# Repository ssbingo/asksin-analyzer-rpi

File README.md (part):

# AskSin-Analyzer

Ein dauerhaft laufender **Funkanalyzer für Homematic (BidCoS, 868 MHz)** auf
Raspberry-Pi-Basis: eine eigene Empfängerplatine hört den Funkverkehr passiv
mit, ein Node.js-Dienst auf dem Pi wertet aus (Duty-Cycle, RSSI,
Telegrammraten), eine Web-UI zeigt an, und ein ioBroker-Adapter spiegelt die
Ergebnisse in die Hausautomation. Mehrere Geräte an verschiedenen Standorten
im Haus sind ausdrücklich vorgesehen.

📖 **[Handbuch (PDF)](docs/handbuch/AskSin-Analyzer-Handbuch.pdf)** — die
anfängertaugliche Schritt-für-Schritt-Anleitung vom Platinenbestellen bis zum
laufenden Gerät.

> ### ⚠️ Platinen mit „HW v0.0.1" im Bestückungsdruck
>
> Bei diesen ist die 2×20-Buchse J1 gespiegelt — direkt aufgesteckt liegt
> jedes Pad auf dem falschen Pi-Pin (5 V auf 3,3 V, Masse auf GPIOs).
> **Nicht ohne den [J1-Rettungsadapter](hardware/kicad/adapter/README.md)
> aufstecken und einschalten.** Mit ihm sind sie voll funktionsfähig.
> Ab **v0.2.0** ist der Fehler behoben, und die Platine liegt neben dem Pi
> statt über dessen Buchsen.

## Projektstand

| Baustein | Stand |
| --- | --- |
| **Hardware v0.2.0** (L-Platine neben dem Pi) | ✅ **in Produktion** (31.07.2026) — DRC/ERC 0/0, 26 Fertigungsprüfungen bestanden |
| Fertigungsdaten (Gerber, BOM, CPL, JLCPCB) | ✅ [`hardware/kicad/fab/`](hardware/kicad/fab/) + Archiv |
| J1-Rettungsadapter für die Chargen v0.0.1 | ✅ [`hardware/kicad/adapter/`](hardware/kicad/adapter/README.md) |
| Firmware | ✅ abgewandelte Fassung des `AskSinSniffer328P` (jp112sdl) — läuft auch ohne Funkmodul und meldet dessen Fehlen, [eigenes Repo](https://github.com/ssbingo/asksin-sniffer-firmware); Prüfwerkzeuge in [`firmware/`](firmware/README.md) |
| Firmware, erweiterte Fassung | 🔨 gebaut, wartet auf die Platine — eigenes Repo [`asksin-sniffer-firmware`](https://github.com/ssbingo/asksin-sniffer-firmware): Versionsauskunft, Folgenummer, Prüfsumme, CC1101-Selbsttest. Im Auslieferungszustand Zeichen für Zeichen wie das Original |
| Mitschnitt der Funkstrecke | ✅ Grundlinie vor Firmware-Änderungen, Schalter unter *Wartung* (F1) |
| Core: Parser + Duty-Cycle | ✅ fertig ([`core/`](core/)) |
| Core: Serial-Ingest, SQLite, CCU-Namen, Analyzer | ✅ fertig verdrahtet (M2–M4) |
| Core: REST-API inkl. XS-Kompat-Endpunkten | ✅ fertig, 108 Unit-Tests gesamt (M5) |
| Web-UI (Nachbau, eigener Code, MIT) | ✅ fertig: Vue 3 + ECharts, vom Core ausgeliefert (M5.5) |
| Demo-Modus (simulierte Anlage) | ✅ fertig, Schalter in den Einstellungen (v0.0.3) |
| Update-Pfade (Core-Self-Update, 328P-Flash) | ✅ fertig (M7.5, v0.0.4) |
| Netzwerkeinstellungen über die Web-UI | ✅ gebaut (M7.6) — Praxistest auf dem Pi ausstehend |
| Status-LED + OLED integriert | ✅ Software fertig (M11) — Hardware-Test steht aus ([`docs/status-led-oled.md`](docs/status-led-oled.md)) |
| Einkaufsführer Zubehör (README + Handbuch) | 📋 geplant (M12, [`docs/einkaufsfuehrer.md`](docs/einkaufsfuehrer.md)) |
| Verbund: 5 Analyzer als Gesamtsystem | ✅ komplett: Dashboard, Matrix+Dedup, Flotten-Update, Langzeitdaten nach InfluxDB (M9.1–M9.5, [`docs/verbund.md`](docs/verbund.md)) |
| Langzeitdaten vor Ort (InfluxDB + Grafana) | ✅ optional auf dem Master: Ein-Klick-Einrichtung, acht fertige Grafana-Ansichten, vier Alarme (M14) |
| Bootmedium | SSD ab Pi 4; **der Pi 3 läuft von SD-Karte** (Netzwerk am USB-Bus, nur USB 2.0) |
| CCU-Verbindungstest mit Diagnose | ✅ nennt die Geräteanzahl, unterscheidet sechs Fehlerursachen und blendet bei fehlender Systemvariable die Einrichtung ein ([`ccu/`](ccu/README.md)) |
| Alarmziele: ioBroker, E-Mail, Telegram | ✅ in der WebUI einstellbar, mit Testversand und deutlichen Fehlermeldungen (M14.2) |
| Versionsabhängigkeit Analyzer ↔ Adapter | ✅ beide Seiten weisen sie aus **und prüfen sie** (M15) |
| Protokoll und Absturzsuche (Tab „Wartung“) | ✅ fertig (M13): Stufen, Tagesrotation, Download, Systemjournal ([`docs/protokoll.md`](docs/protokoll.md)) |
| ioBroker-Adapter | 🔨 Grundgerüst steht (M6, eigenes Repo [`ioBroker.asksinanalyzer-rpi`](https://github.com/ssbingo/ioBroker.asksinanalyzer-rpi), MIT, mehrinstanzfähig) |

## Installation auf dem Raspberry Pi

Ein Aufruf installiert und konfiguriert alles (Details: [`deploy/README.md`](deploy/README.md)):

```bash
curl -fsSL https://raw.githubusercontent.com/ssbingo/asksin-analyzer-rpi/main/install.sh | sudo bash
```

## Aufbau des Repositories

```
hardware/                 Platine, Bestelllisten, Setup-Skripte
├── README.md             vollständige Hardware-Spezifikation
├── bestellliste-reichelt.md
├── setup-uart.sh         richtet den Pi-UART ein (Pi 3/4/5)
├── 99-asksin-analyzer.rules   udev: fester Gerätename
├── 3d-druck/             Druckvorlagen 19″-Einbaurahmen (folgen nach Testdruck)
├── datasheets/           Ebyte-E07-Serienspezifikation
└── kicad/                KiCad-9-Projekt, generiert & maschinell geprüft
    ├── generate_*.py     Schaltplan, Layout, Symbole, Footprints, BOM/CPL
    ├── autoroute.py      Freerouting-Anbindung
    ├── rebuild.py       baut die Platine neu, bis alle Prüfungen sauber sind
    ├── adapter/         J1-Rettungsadapter für die Chargen v0.0.1
    ├── fab/             Gerber, Bohrdaten, BOM, CPL, PDFs
    └── AskSin-Analyzer-V3-fertigung.zip   Upload-Paket
core/                     Node.js/TypeScript-Analysedienst
webui/                    Web-UI-Nachbau (Vue 3 + ECharts, MIT)
deploy/                   systemd-Unit, Beispielkonfig, CLI-Wrapper
install.sh / update.sh    Ein-Befehl-Installation und -Update auf dem Pi
docs/
├── serial-protocol.md    das serielle Telegrammformat, verifiziert
├── raspberry-pi-uart.md  UART-Konfiguration Pi 3/4/5
├── webui-und-updates.md  API-Vertrag der Web-UI, Update-Pfade, Lizenzlage
├── verbund.md            Phase M9: fünf Analyzer als Gesamtsystem (Föderation)
├── protokoll.md          Phase M13: Protokoll, Systemjournal, Absturzsuche
├── status-led-oled.md    Phase M11: Status-LED (PWM/SPI) und OLED
└── handbuch/             das Handbuch (HTML-Quelle, Bilder, PDF)
reference/                Originalprojekte (nicht eingecheckt — siehe unten)
```

## Die Kernentscheidungen in einem Absatz

Die Funkseite bleibt beim bewährten Gespann **ATmega328P + CC1101** mit der
unveränderten `AskSinSniffer328P`-Firmware — kein Fork, wer will flasht die
Original-HEX. Die Platine ist ein **L-förmiger** Aufsatz, der auf den
durchgeschleiften Header des PoE-HAT gesteckt wird; der Streifen liegt
**parallel neben dem Pi** an der Header-Seite, höchstens 20 mm breit, und
deckt keine Buchse ab. Der Schenkel steht 32 mm **hinter** der SD-Kante —
dort sitzt das Funkmodul, weit weg vom Störnebel und direkt am rückwärtigen
Antennen-Keystone. Die Antenne verlässt das
Ebyte-Modul per IPEX — auf der Platine existiert **keine einzige HF-Leitung**.
Der bekannte 2,12-%-Baudratenfehler der 8-MHz-Klasse wird nicht in der
Firmware „repariert", sondern auf der Pi-Seite kompensiert: der Port läuft mit
**58824 Baud** (Details: [`hardware/README.md`](hardware/README.md),
Abschnitt 2.5 — das ist Absicht, nicht Tippfehler). Analyse-Software und
ioBroker-Adapter sind getrennt geschnitten, damit der Adapter frei lizenzierbar
und veröffentlichbar bleibt ([`docs/webui-und-updates.md`](docs/webui-und-updates.md),
Abschnitt 4).

## Schnellzugriffe

- **Platine nachbestellen:** `hardware/kicad/AskSin-Analyzer-V3-fertigung.zip`
  hochladen (4 Lagen, 1,6 mm); SMD-Bestückung mit
  `fab/jlcpcb_bom.csv` + `fab/jlcpcb_cpl.csv`
- **Bauteile kaufen:** [`hardware/bestellliste-reichelt.md`](hardware/bestellliste-reichelt.md)
- **Pi einrichten:** `sudo hardware/setup-uart.sh` → Neustart →
  `stty -F /dev/ttyAMA0 57600 raw -echo` — dann die exakte Rate:
  `sudo python3 deploy/baudrate.py /dev/ttyAMA0 58824 && cat -v /dev/ttyAMA0`
  (`stty` kennt nur genormte Raten und lehnt 58824 ab)
- **Core-Tests:** `cd core && npm install && npm run check`

## Versionierung

Ein Repository, drei unabhängige Zählungen über Tag-Präfixe:

| Tag | versioniert | aktuell |
| --- | --- | --- |
| `hardware-vX.Y.Z` | die Platine (Schaltplan, Layout, Fertigungsdaten) | **0.2.0** — steht auch im Bestückungsdruck |
| `core-vX.Y.Z` | die Pi-Software (`core/` + `webui/`, deren `package.json` führen dieselbe Nummer) | **1.2.0** |
| `vX.Y.Z` | den Gesamtstand des Projekts (Doku, Handbuch, Zusammenspiel) | **1.2.0** |

Die **Firmware hat ein eigenes Repository** mit eigener Versionierung:
[ssbingo/asksin-sniffer-firmware](https://github.com/ssbingo/asksin-sniffer-firmware).
Sie war ursprünglich die unveränderte `AskSinSniffer328P` von jp112sdl; seit
den Erweiterungen um Folgenummer, Prüfsumme, Versionsauskunft und
Funkmodul-Selbsttest ist sie eine abgewandelte Fassung und wird als solche
gepflegt — Lizenz unverändert CC BY-NC-SA 3.0. Der ioBroker-Adapter bekommt
ebenfalls ein eigenes Repository mit eigenständiger Versionierung.

## Changelog

### v1.8.0 — 26.08.2026

**Neue Ansicht „Funklast": Wer verbraucht die Sendezeit — und wie viel davon war umsonst?**

Entstanden aus einem echten Fall: Die CCU meldete für ein LAN-Gateway einen
Duty-Cycle über 100 %, und die Ursache zu finden kostete eine Stunde Handarbeit
an der Datenbank. Dieselbe Kette läuft jetzt automatisch — an denselben Daten
gemessen in **53 ms**.

- Die Spalten stehen in der Reihenfolge der Ursachen: **Sendezeit → Bursts →
  Wiederholungen → vergebliche Wiederholungen.** Ein Absender fällt durch
  Sendezeit auf, nicht durch die Zahl der Telegramme; im Fall stieg die Zahl von
  219 auf 345, die Sendezeit aber von 4,6 s auf 30 s.
- **„Vergeblich" kann nur ein Mithörer füllen:** Wiederholungen, obwohl der
  Analyzer die Antwort bereits gehört hatte. Eine Zentrale sieht nur, dass sie
  wiederholen muss — nicht, ob die Antwort unterwegs verloren ging. Steht dort
  eine hohe Zahl, ist der Rückweg das Nadelöhr, und man sucht am Absender statt
  am Gerät.
- **Mehrere Sender unter einer Adresse werden getrennt.** Alle LAN-Gateways
  einer CCU senden mit deren Adresse; auseinanderhalten lässt sie nur die
  Empfangsstärke. Im Fall: zwei Gipfel, 30 dB auseinander, und 78 von 81 Bursts
  aus dem lauten — damit war das schuldige Gateway benannt, unabhängig von der
  CCU-Anzeige.
- Aufklappen zeigt je Gegenstelle die Sendungen je Vorgang, die Bursts, die
  vergeblichen Wiederholungen und wie laut der Analyzer die **Antworten** hört.
  Dazu ein Satz, was zu tun ist — nicht nur, was gemessen wurde.
- Zehn Tests, darunter der komplette Fall als Durchlauf. Zwei Fehler fanden sie
  beim Schreiben: HmIP beginnt bei Typ 0x80 (mein Testwert 0x5E war das
  Leistungstelegramm eines Schaltaktors und prüfte nichts), und ein Gerät, das
  in einem Fenster **nur quittiert**, fiel ganz aus der Liste — seine Sendezeit
  belegt das Band trotzdem.
- Handbuch 13.4 liest den Fall Zeile für Zeile mit; 13.5 und 13.6 rücken auf.

### v1.7.3 — 25.08.2026

**Nachtrag zur „Sammlung": Der Master fragte sich selbst über HTTP.**

In v1.7.2 lief der Master beim Zählen über *alle* Peers — und die Liste enthält
ihn selbst. Sein Aufruf von `/api/langzeitdaten` rief also wieder die Zählung
auf, die wieder sich selbst aufrief. Das endet erst in Zeitüberschreitungen, und
die Kachel zeigte danach wieder einen Strich — aus dem genau umgekehrten Grund
als vorher.

- Der eigene Standort wird jetzt **direkt** genommen, ohne HTTP; nur die
  entfernten Peers werden gefragt.
- Ein Test hält es fest, gegengeprüft.
- Nebenbei die Wortwahl berichtigt: Ein Analyzer ohne Schreibvorgang heißt
  „liefert gerade nicht" statt „seit Längerem still". Direkt nach jeder
  Aktualisierung steht dort für einen Schreibtakt lang auch ein völlig gesundes
  Gerät — beobachtet an Dachboden unmittelbar nach dem Rollout.

### v1.7.2 — 25.08.2026

**„Sammlung" zeigt wieder, wie viele Standorte liefern — statt eines Strichs.**

Gemeldet: „Was sollte eigentlich bei dem Punkt *Sammlung* stehen? Dort ist
bisher nur ein Strich zu finden." Antwort: **3 Standorte**. Dass dort nichts
stand, war ein stiller Fehler aus unserer eigenen Token-Trennung.

Die Zeile zählte die Standorte mit einer Flux-Abfrage. Die lief — bis Grafana
einen **Lese**- und die Analyzer einen **Schreib**-Token bekamen. Seither sieht
ein Analyzer den Bucket nicht mehr, und InfluxDB antwortet nicht mit „verboten",
sondern mit `HTTP 404 could not find bucket`. Der `catch` machte daraus ein
stilles „nicht ermittelbar".

- **Gezählt werden jetzt die Analyzer, nicht die Datenbank.** Jeder weiß über
  sich selbst, ob und wann sein letzter Schreibvorgang geglückt ist; der Master
  fragt der Reihe nach alle ab. Kein Lesezugriff nötig — die Token-Trennung
  bleibt, wie sie ist.
- Der ursprüngliche Anspruch bleibt: **Ein Standort zählt nur, wenn er wirklich
  schreibt.** Fehlt einer, steht dort *2 von 3 Standorten*; wer fehlt, zeigt der
  Mauszeiger.
- Ein Standort gilt erst nach **drei Schreibtakten** ohne Erfolg als still,
  mindestens aber nach fünf Minuten — ein einzelner Aussetzer darf die Anzeige
  nicht flackern lassen.
- `tools/pruefe-influx-lesezugriff.sh` hält fest, dass der Core nicht wieder
  anfängt zu lesen. Gegengeprüft.
- Handbuch 19.6 erklärt die ganze Kachel und warum nicht die Datenbank gefragt
  wird.

### v1.7.1 — 24.08.2026

**Die Clients melden jetzt über den Master.**

Damit fällt die Grenze aus v1.7.0: Bisher meldete sich nur der Master, weil nur
dort ein Alarmziel eingerichtet wird.

- **Der Master holt ab, die Clients senden nicht.** Das folgt der Richtung, die
  der Verbund ohnehin hat: Der Master kennt jeden Client samt Token, die Clients
  kennen den Master nicht. Ein Push bräuchte auf jedem Client Adresse und
  Geheimnis des Masters — neue Einstellungen, die jemand pflegen muss. So kommt
  die Weiterleitung **ohne eine einzige neue Einstellung** aus.
- **In der Nachricht steht der Standort des Clients**, nicht der des Masters.
  Der Master reicht den Text weiter, den der Client selbst gebaut hat.
- **Nichts geht verloren:** Der Client hakt eine Meldung erst ab, wenn der
  Master die Zustellung bestätigt hat. Ist der Master aus, bleibt sie liegen und
  geht beim nächsten Umlauf hinaus. Angestaut wird nichts — es gibt immer nur
  den letzten Lauf.
- **Die Nachricht nennt jetzt das Datum des Laufs**, nicht nur die Dauer: Eine
  verspätete Weiterleitung läse sich sonst so, als sei es eben erst passiert.
- Zwei Tests halten den Vertrag fest: dass beide Seiten die Abhak-Schnittstelle
  gleich verstehen (`httpPost` schickt bewusst keinen Rumpf, die Aktion steht
  in der Abfragezeichenkette), und dass der Master **erst zustellt und dann
  abhakt**. Beides gegengeprüft.

### v1.7.0 — 24.08.2026

**Der Analyzer meldet, wenn eine Systemaktualisierung durchgelaufen ist.**

Auf Wunsch — dritter Schalter im selben Feld. Zugestellt über **dasselbe Ziel,
das schon für die Alarme eingerichtet ist**: ioBroker-Adapter, E-Mail oder
Telegram. Ist dort nichts eingerichtet oder der Versand aus, bleibt der Schalter
ausgegraut, mit dem Hinweis wo man das ändert; ein Schalter, der sich umlegen
lässt und nichts bewirkt, wäre schlimmer als keiner.

- **Der Adapter braucht keine Änderung.** Die Meldung geht im
  Grafana-Webhook-Format hinaus, also in genau der Form, die er für die Alarme
  ohnehin versteht.
- **Erfolg und Fehlschlag** werden gemeldet. Der Fehlschlag ist der wichtigere
  Fall: Ein Gerät, das seit Wochen vergeblich aktualisiert, sieht von außen aus
  wie eines, das brav aktualisiert.
- Die Nachricht nennt Standort, Paketanzahl, Dauer und ob ein Neustart nötig
  ist. War nichts nachzuholen, steht das ausdrücklich da — „0 Pakete" allein
  liesse den Empfänger raten, ob die Meldung abgeschnitten ist.
- **Eine Entwarnung folgt sofort nach.** Sonst bliebe `alarm.aktiv` im Adapter
  dauerhaft auf *wahr*, denn eine abgeschlossene Aktualisierung ist ein Ereignis
  und kein andauernder Zustand. Weitergeleitet wird die Entwarnung nur, wenn man
  das ausdrücklich eingestellt hat — es kommt also genau eine Nachricht an.
- **Übersteht den Neustart des Dienstes mitten im Lauf:** apt rüstet auch
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
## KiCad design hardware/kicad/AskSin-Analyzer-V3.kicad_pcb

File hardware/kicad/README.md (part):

# KiCad-Projekt AskSin-Analyzer V4

KiCad 9. Schaltplan und Layout werden **generiert**, geroutet wird mit
Freerouting.

Stand: **ERC 0 Fehler, 0 Warnungen · DRC 0 Verstöße.** Netzliste stimmt exakt
mit der Spezifikation überein — 32 Bauteile, 25 Netze, 111 Anschlüsse. Platine
vollständig verdrahtet: 330 Leiterbahnen, 157 Durchkontaktierungen, vier Lagen.

## Ablauf

```bash
python3 generate_module_symbol.py     # Symbol des Funkmoduls
python3 generate_module_footprint.py  # Footprint des Funkmoduls
python3 generate_schematic.py         # Schaltplan, Projektdateien, netlist.md
python3 generate_pcb.py               # Umriss, Platzierung, Netze, Flächen
python3 autoroute.py                  # Freerouting + Flächenanbindung

kicad-cli sch erc --output erc.rpt --severity-all AskSin-Analyzer-V3.kicad_sch
kicad-cli sch export netlist --output netlist.net AskSin-Analyzer-V3.kicad_sch
python3 verify_netlist.py netlist.net
kicad-cli pcb drc --output drc.rpt --severity-error AskSin-Analyzer-V3.kicad_pcb
```

⚠️ **Freerouting arbeitet mit Zufallselementen.** Zwei Läufe auf derselben
Eingabe liefern unterschiedliche Ergebnisse — mal null Verstöße, mal zwei bis
drei offene Verbindungen. Die geroutete Platinendatei gehört deshalb ins
Repository und wird **nicht** bei jedem Bauen neu erzeugt. Wer neu routet, prüft
anschließend den DRC.

## Warum generiert

Die Netzliste steht in `generate_schematic.py` und ist die einzige Quelle der
Wahrheit. `verify_netlist.py` liest KiCads eigenen Netzlisten-Export zurück und
vergleicht ihn Knoten für Knoten — der Generator kann eine formal gültige Datei
schreiben, die trotzdem falsch verdrahtet ist.

Der Generator prüft vorab auf Pins in mehreren Netzen und auf Platzierungen, die
sich überlappen, den Umriss verlassen oder auf einer Bohrung liegen. Beides hat
echte Fehler gefangen: der Koppelkondensator C8 der Reset-Strecke war
versehentlich zusätzlich auf Masse gelegt, und der erste Platzierungsentwurf
hatte elf Überlappungen, aus denen der DRC 85 Folgefehler machte — darunter
sechs „Kurzschlüsse", die alle dieselbe Ursache hatten.

## Bauform

L-förmig, 118 × 46 mm umschließend, 3380 mm². Ein schmaler **Arm** trägt die
2×20-Buchse über dem durchgeschleiften Header des Waveshare-PoE-HAT, der
**Körper** sitzt rechts daneben außerhalb des Stapels. Der Lüfter bleibt frei,
und das Funkmodul liegt nicht zwischen zwei Schaltreglern, HDMI und USB3.

Position der Buchse und die beiden Bohrungen im Arm stammen aus der offiziellen
KiCad-Vorlage `RaspberryPi-HAT`. Die beiden hinteren Bohrungen stützen den
auskragenden Körper; **KB1/KB2** sind Kabelbinderlöcher als Zugentlastung für
das Antennenkabel.

## Lagenaufbau

| Lage | Belegung |
| --- | --- |
| F.Cu | Signale, Masseauffüllung |
| In1.Cu | durchgehende Masse |
| In2.Cu | durchgehende Masse |
| B.Cu | Signale, Masseauffüllung |

Ursprünglich lag +3V3 auf In2. Das zwang jedem Versorgungspad ein eigenes
Stützvia auf, wofür in der fertig gerouteten Platine regelmäßig der Platz
fehlte — sieben Pads blieben offen. Das Netz zieht rund 25 mA; als Leiterbahn
mit 0,6 mm ist es reichlich bemessen. Zwei durchgehende Masseflächen schirmen
den Empfänger zudem besser ab. Nach der Umstellung routete Freerouting alle
52 Netze ohne Rest.

Die Anbindung ist **`THT_THERMAL`**: Durchsteckpads bekommen eine thermische
Entlastung, SMD-Pads sind voll angebunden. Die Platine wird von Hand bestückt,
und dort sind die Durchsteckpins das Problem — ihr Pin berührt die Massefläche
auf allen vier Lagen. Volle Anbindung an allen Pads, wie ursprünglich gesetzt,
hätte die acht Massepins der 40-poligen Buchse praktisch unlötbar gemacht.
Umgekehrt ließe eine Entlastung auch der SMD-Pads am TQFP-32 mit 0,8 mm Raster
nicht genug Speichen zu — der DRC meldet das als `starved_thermal`.

## Was der Weg über Freerouting sichtbar gemacht hat

**Die Zonenumrisse waren offene Polygonzüge.** KiCad meldet das nur als
Warnung, aber es war die Ursache eines Absturzes beim Füllen. `SetClosed(True)`
behebt es.

**Die Umrandung im Specctra-Export hat Breite 0** — Freerouting darf dann bis
exakt an die Platinenkante routen. Die Breite zu erhöhen macht es schlimmer:
Freerouting liest die Umrandung dann als Linie statt als geschlossene Grenze und
routet quer durch die Aussparung des L. Von 2 auf 21 Kantenverstöße. Richtig
ist, den Umriss selbst im DSN um 0,55 mm nach innen zu schrumpfen.

**Kleinere Stützvias sparen keinen Platz.** 0,45 mm Durchmesser mit 0,25 mm
Bohrung erzeugte 52 neue Verstöße, weil es die eigenen Entwurfsregeln
unterschritt: 0,3 mm ist die Bohrungsuntergrenze, und mit 0,13 mm Restring folgt
daraus mindestens 0,56 mm Durchmesser.

## Flächenanbindung

Freerouting behandelt die Innenlagen als Versorgungslagen und lässt sie
unangetastet — setzt dorthin aber auch keine Durchkontaktierungen.
`autoroute.py` ergänzt sie in drei Schritten:

1. **Pad-Anbindung** — jeder Massepin bekommt eine Durchkontaktierung, der Weg
   dorthin wird mit A*-Suche gelegt.
2. **Via-Raster** im 3-mm-Abstand über die ganze Platine. Bindet die Auffüllung
   der Außenlagen an die Innenlagen und verbessert die Masseführung unter dem
   Funkmodul.
3. **Gezielte Inselanbindung** — die Auffüllung zerfällt durch die Leiterbahnen
   in Teilflächen; solche ohne Pad und ohne Durchkontaktierung meldet der DRC
   als offene Verbindung. Der Schritt sucht sie mit einem exakten
   Punkt-in-Fläche-Test und setzt gezielt eine Durchkontaktierung hinein.
   Wiederholt, weil jede neue Durchkontaktierung die Auffüllung verändert und
   dabei neue Teilflächen entstehen können.

Schritt 3 war nötig: ein gleichmäßiges Raster allein ließ zuverlässig zwei bis
drei Inseln übrig, unabhängig von der Rasterweite.

## Dateien

| Datei | Rolle |
| --- | --- |
| `generate_schematic.py` | Netzliste, Bestückung — hier wird geändert |
| `generate_module_symbol.py` | Symbol des CC1101-Moduls, 22 Pins |
| `generate_module_footprint.py` | Footprint aus den Datenblattmaßen |
| `generate_pcb.py` | Umriss, Platzierung, Netze, Flächen |
| `autoroute.py` | Freerouting-Durchlauf und Flächenanbindung |
| `route_pcb.py` | eigener Rasterrouter — Wegsuche und Via-Setzung, von `autoroute.py` mitbenutzt |
| `verify_netlist.py` | vergleicht KiCads Netzlisten-Export mit der Vorgabe |
| `netlist.md` | menschenlesbare Netzliste zur Gegenprobe |
| `erc.rpt`, `drc.rpt`, `bom.csv`, `*.pdf` | Prüf- und Review-Artefakte |

## Funkmodul

`U3` ist ein **Ebyte E07-900M10S** — CC1101, 855–925 MHz, 14 × 20 mm,
22 Halblöcher im 1,27-mm-Raster, IPEX-Antennenbuchse.

Symbol und Footprint sind gegen
[`../datasheets/Ebyte_E07-M_series_specification.pdf`](../datasheets/)
Abschnitt 3.2 verifiziert. Die Maßkette schließt exakt:
`2,00 + 7 × 1,27 + 5,57 + 2 × 1,27 + 1,00 = 20,00 mm`. Das Datenblatt gibt Ober-
und Unterkantenabstand unabhängig an; der Generator bricht ab, wenn die Kette
nicht aufgeht.

⚠️ Beim Einkauf: `E07-900M10S`, **nicht** `E07-900MM10S` — Letzterer ist
10 × 10 mm groß und hat kein IPEX, nur Stanzlöcher.

## Voraussetzungen

```bash
sudo apt install kicad
sudo apt install openjdk-25-jre-headless      # Freerouting 2.x braucht Java 25
mkdir -p ~/.local/share/freerouting
curl -L -o ~/.local/share/freerouting/freerouting-2.2.4.jar \
  https://github.com/freerouting/freerouting/releases/download/v2.2.4/freerouting-2.2.4.jar
```

`autoroute.py` sucht sich das neueste JAR, das mit der installierten
Java-Version wirklich startet, und meldet klar, was fehlt.

## Was noch fehlt

- Bestückungsdruck aufräumen: die Bezeichner stehen an Vorgabepositionen und
  überlappen teils. Für die Fertigung unkritisch, für die Bestückungskontrolle
  unschön.
- 3D-Modelle sind nicht installiert; die Darstellung zeigt nur Pads.
- Lagenaufbau und Impedanz mit dem Fertiger abstimmen.

## Lizenz

Abgeleitet von **AskSin-Analyzer-XS-RPi V1.1** (der-pw), CC BY-NC-SA 4.0.
Diese Ableitung steht unter derselben Lizenz. Namensnennung ist Pflicht.

## Fertigungsprüfung

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
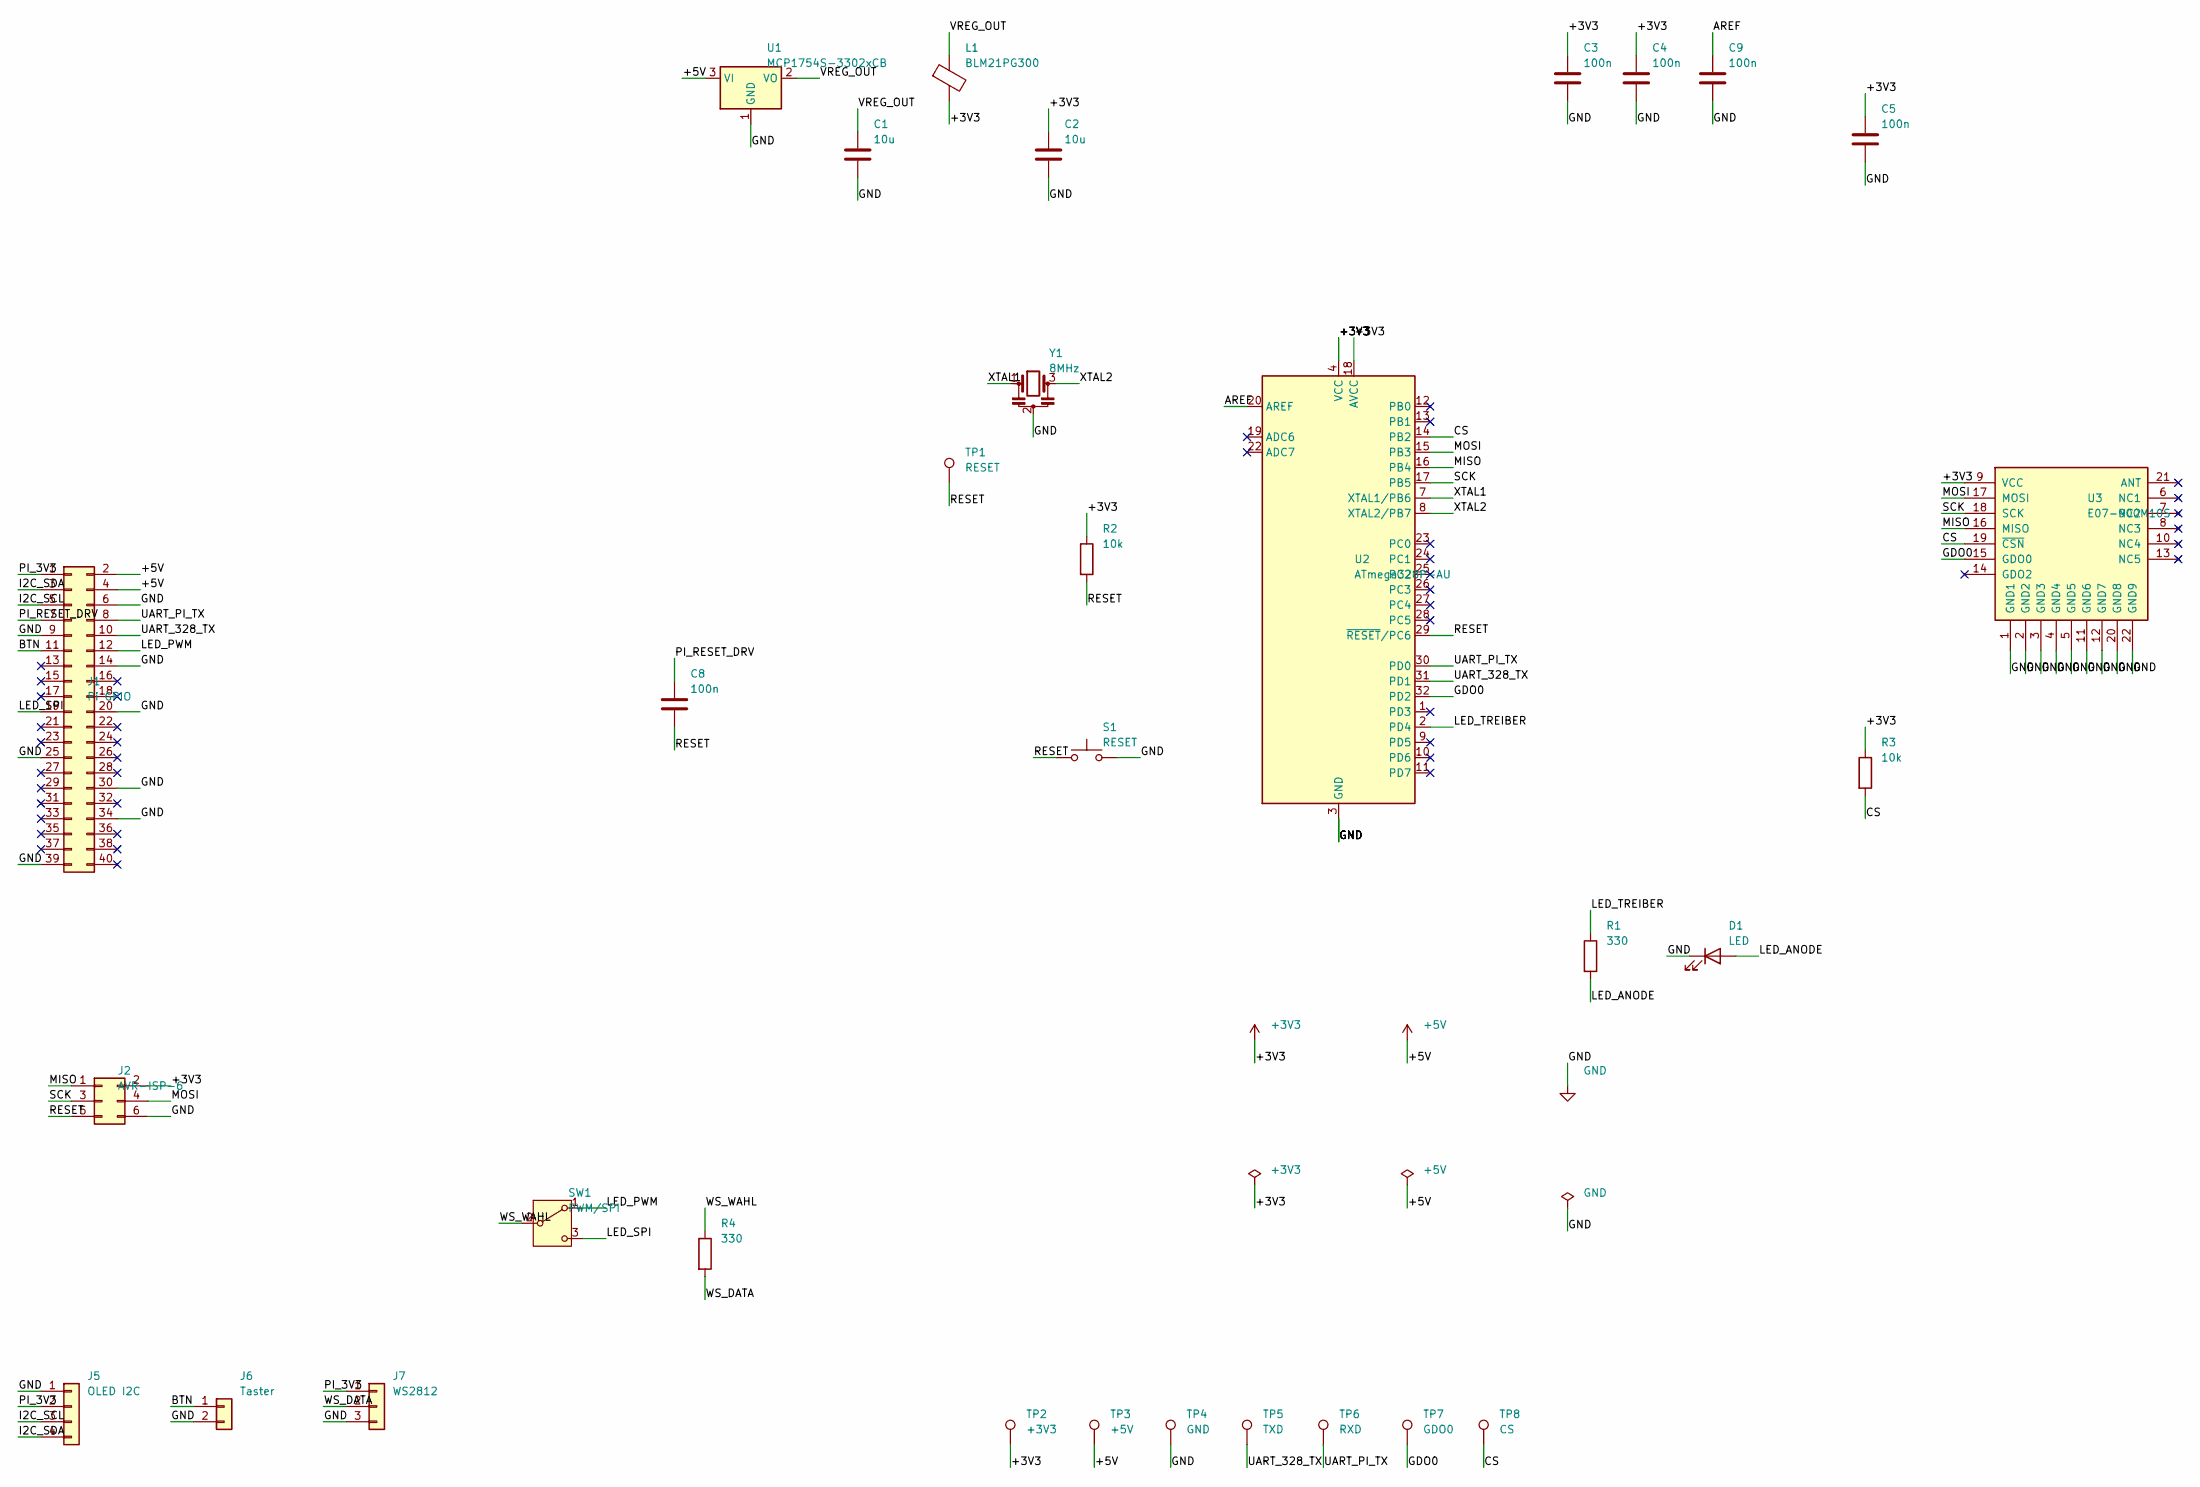
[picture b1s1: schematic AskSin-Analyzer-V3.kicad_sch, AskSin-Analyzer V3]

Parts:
C1, C2: 10u; C_0805_2012Metric_Pad1.18x1.45mm_HandSolder
C3, C4, C5, C8, C9: 100n; C_0805_2012Metric_Pad1.18x1.45mm_HandSolder
D1: LED; LED_0805_2012Metric_Pad1.15x1.40mm_HandSolder
J1: Pi GPIO; PinSocket_2x20_P2.54mm_Vertical
J2: AVR-ISP-6; PinHeader_2x03_P2.54mm_Vertical
J5: OLED I2C; JST_PH_B4B-PH-K_1x04_P2.00mm_Vertical
J6: Taster; JST_PH_B2B-PH-K_1x02_P2.00mm_Vertical
J7: WS2812; JST_PH_B3B-PH-K_1x03_P2.00mm_Vertical
L1: BLM21PG300; L_0805_2012Metric_Pad1.15x1.40mm_HandSolder
R1, R4: 330; R_0805_2012Metric_Pad1.20x1.40mm_HandSolder
R2, R3: 10k; R_0805_2012Metric_Pad1.20x1.40mm_HandSolder
S1: RESET; SW_SPST_B3U-1000P-B
SW1: PWM/SPI; SW_SPDT_CK_JS102011SAQN
TP1: RESET; TestPoint_Pad_1.0x1.0mm
TP2: +3V3; TestPoint_Pad_1.0x1.0mm
TP3: +5V; TestPoint_Pad_1.0x1.0mm
TP4: GND; TestPoint_Pad_1.0x1.0mm
TP5: TXD; TestPoint_Pad_1.0x1.0mm
TP6: RXD; TestPoint_Pad_1.0x1.0mm
TP7: GDO0; TestPoint_Pad_1.0x1.0mm
TP8: CS; TestPoint_Pad_1.0x1.0mm
U1: MCP1754S-3302xCB; SOT-23
U2: ATmega328P-AU; TQFP-32_7x7mm_P0.8mm
U3: E07-900M10S
Y1: 8MHz; Resonator_Murata_CSTLSxxxX-3Pin_W5.5mm_H3.0mm

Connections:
+3V3: C2.1, C3.1, C4.1, C5.1, J2.2, L1.2, R2.1, R3.1, TP2.1, U2.4 (VCC), U2.6 (VCC), U2.18 (AVCC), U3.9 (VCC)
+5V: J1.2, J1.4, TP3.1, U1.3 (VI)
AREF: C9.1, U2.20 (AREF)
BTN: J1.11, J6.1
CS: R3.2, TP8.1, U2.14 (PB2), U3.19 (~CSN)
GDO0: TP7.1, U2.32 (PD2), U3.15 (GDO0)
GND: C1.2, C2.2, C3.2, C4.2, C5.2, C9.2, D1.1 (K), J1.6, J1.9, J1.14, J1.20, J1.25, J1.30, J1.34, J1.39, J2.6, J5.1, J6.2, J7.3, S1.2, TP4.1, U1.1 (GND), U2.3 (GND), U2.5 (GND), U2.21 (GND), U3.1 (GND1), U3.2 (GND2), U3.3 (GND3), U3.4 (GND4), U3.5 (GND5), U3.11 (GND6), U3.12 (GND7), U3.20 (GND8), U3.22 (GND9), Y1.2
I2C_SCL: J1.5, J5.3
I2C_SDA: J1.3, J5.4
LED_ANODE: D1.2 (A), R1.2
LED_PWM: J1.12, SW1.1 (A)
LED_SPI: J1.19, SW1.3 (C)
LED_TREIBER: R1.1, U2.2 (PD4)
MISO: J2.1, U2.16 (PB4), U3.16 (MISO)
MOSI: J2.4, U2.15 (PB3), U3.17 (MOSI)
PI_3V3: J1.1, J5.2, J7.1
PI_RESET_DRV: C8.1, J1.7
RESET: C8.2, J2.5, R2.2, S1.1, TP1.1, U2.29 (~RESET/PC6)
SCK: J2.3, U2.17 (PB5), U3.18 (SCK)
UART_328_TX: J1.10, TP5.1, U2.31 (PD1)
UART_PI_TX: J1.8, TP6.1, U2.30 (PD0)
VREG_OUT: C1.1, L1.1, U1.2 (VO)
WS_DATA: J7.2, R4.2
WS_WAHL: R4.1, SW1.2 (B)
XTAL1: U2.7 (XTAL1/PB6), Y1.1
XTAL2: U2.8 (XTAL2/PB7), Y1.3

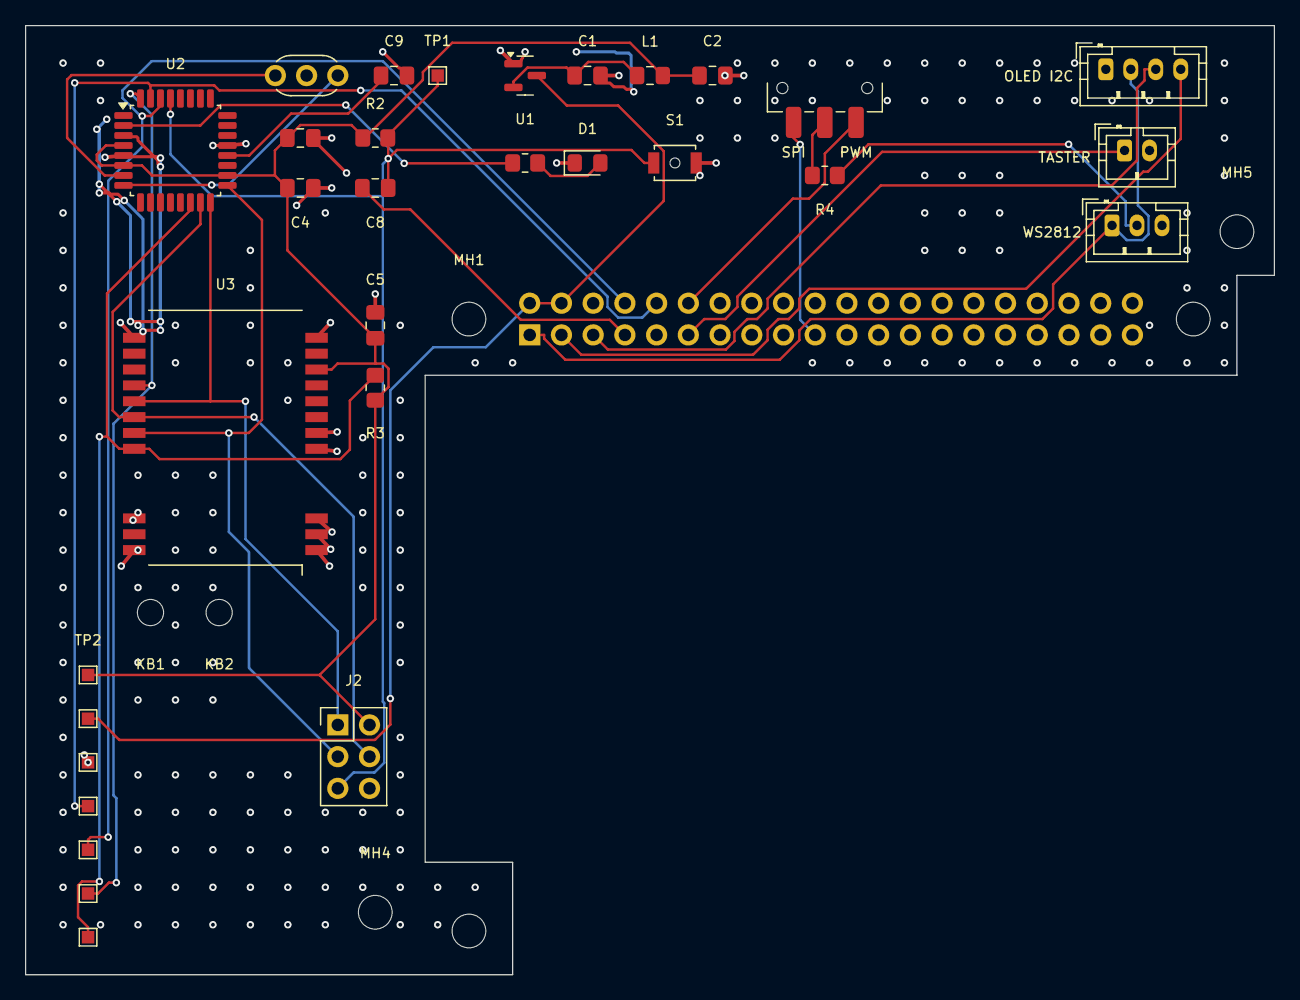
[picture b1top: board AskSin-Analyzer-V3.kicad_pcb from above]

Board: 4 copper layers, 100.0 x 76.0 mm, 39 parts (1 on the bottom side), 26 nets.

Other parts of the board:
KB1, KB2: MountingHole_2.1mm
MH1, MH2, MH3, MH4, MH5: MountingHole_2.7mm_M2.5

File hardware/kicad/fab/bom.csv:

Comment,Designator,Footprint,Quantity,Mounting,Source
10u,"C1,C2",C_0805_2012Metric_Pad1.18x1.45mm_HandSolder,2,SMD,Reichelt CL21A106KOQNNNG
100n,"C3,C4,C5,C8,C9",C_0805_2012Metric_Pad1.18x1.45mm_HandSolder,5,SMD,Reichelt KEM X7R0805 100N
LED,D1,LED_0805_2012Metric_Pad1.15x1.40mm_HandSolder,1,SMD,Reichelt EVL 17-21USRC
Pi GPIO,J1,PinSocket_2x20_P2.54mm_Vertical,1,THT,Reichelt MPE 094-2-040
AVR-ISP-6,J2,PinHeader_2x03_P2.54mm_Vertical,1,THT,Reichelt ECON SL6G2
OLED I2C,J5,JST_PH_B4B-PH-K_1x04_P2.00mm_Vertical,1,THT,Reichelt JST PH4P ST
Taster,J6,JST_PH_B2B-PH-K_1x02_P2.00mm_Vertical,1,THT,Reichelt JST PH2P ST
WS2812,J7,JST_PH_B3B-PH-K_1x03_P2.00mm_Vertical,1,THT,Reichelt JST PH3P ST
BLM21PG300,L1,L_0805_2012Metric_Pad1.15x1.40mm_HandSolder,1,SMD,Reichelt BLM21PG300SN1D
330,"R1,R4",R_0805_2012Metric_Pad1.20x1.40mm_HandSolder,2,SMD,Reichelt WAL WR08X3300FTL
10k,"R2,R3",R_0805_2012Metric_Pad1.20x1.40mm_HandSolder,2,SMD,Reichelt WAL WR08X1002FTL
RESET,S1,SW_SPST_B3U-1000P-B,1,SMD,JLCPCB C231329 (B3U-1000P)
PWM/SPI,SW1,SW_SPDT_CK_JS102011SAQN,1,SMD,JLCPCB C221660 (C&K JS102011SAQN)
MCP1754S-3302xCB,U1,SOT-23,1,SMD,Reichelt MCP 1754-3302CB
ATmega328P-AU,U2,TQFP-32_7x7mm_P0.8mm,1,SMD,Reichelt ATMEGA 328P-AU
E07-900M10S,U3,E07-900M10S,1,SMD,Ebyte E07-900M10S — nicht bei Reichelt
8MHz,Y1,Resonator_Murata_CSTLSxxxX-3Pin_W5.5mm_H3.0mm,1,THT,JLCPCB C83707 (CSTLS8M00G53-B0)

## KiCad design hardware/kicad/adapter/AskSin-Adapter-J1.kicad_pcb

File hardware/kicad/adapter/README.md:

# J1-Rettungsadapter (für Platinen der Hardware v0.0.1)

> ⚠️ **Warum es dieses Bauteil gibt:** Auf allen 2026 gefertigten Platinen
> (Bestückungsdruck „HW v0.0.1") ist die 2×20-Buchse J1 gespiegelt. Direkt auf
> den Pi gesteckt landet jedes Pad auf dem falschen Pi-Pin — 5 V auf 3,3 V,
> Masse auf GPIOs. **Diese Platinen niemals ohne Adapter aufstecken und
> einschalten.** Mit dem Adapter sind sie voll funktionsfähig.

## Das Fehlerbild, ausgemessen

Alle Maße ab der vorderen Platinenkante (der Kante, die beim Pi zur
Platinenkante zeigt):

| | gerade Pins (2, 4, 6 …) | ungerade Pins (1, 3, 5 …) |
| --- | --- | --- |
| Raspberry Pi / PoE-HAT | **2,23 mm** | 4,77 mm |
| Analyzer-Platine v0.0.1 | **7,31 mm** | 4,77 mm |

Die ungerade Reihe sitzt richtig; die gerade liegt nicht *zwischen* ungerader
Reihe und Kante, sondern dahinter. Kein einziger Pin trifft.

## Wie der Adapter das löst

Nicht durch Umsortieren einzelner Reihen, sondern indem das **ganze Steckbild
um 2,54 mm nach hinten versetzt** wird — dann stimmt die Reihenfolge wieder:

```text
    ┌───────────────────────────┐  Analyzer-Platine (v0.0.1)
    │  Buchse 2x20 (unten dran) │
    └──┬───────────────────────┬┘
       │ Stiftleiste 2x20      │     ← Adapter oben, Reihen 7,31 / 9,85 mm
    ┌──┴───────────────────────┴──┐
    │        A D A P T E R        │  65 × 14 mm, 2 Lagen
    └──┬───────────────────────┬──┘
       │ Buchsenleiste 2x20    │     ← Adapter unten, Reihen 2,23 / 4,77 mm
    ┌──┴───────────────────────┴──┐
    │  Stiftleiste des PoE-HAT    │
    └─────────────────────────────┘
```

Jeder Pin geht schnurstracks von unten nach oben: Pin n der Buchse auf Pin n
der Stiftleiste. Die ungeraden Bahnen laufen 2,54 mm auf der Oberseite, die
geraden 7,62 mm auf der Unterseite an den Pads vorbei. Keine Durchkontaktierung
nötig — bedrahtete Pads liegen ohnehin auf beiden Lagen.

## Stückliste — zwei Standardteile

| Ref | Bauteil | Lage | JLCPCB |
| --- | --- | --- | --- |
| **J1** | Buchsenleiste **2×20**, RM 2,54, gerade, Höhe 8,5 mm | **unten** (Körper zeigt zum PoE-HAT) | **C2977589** (ZHOURI), Extended |
| **J2** | Stiftleiste **2×20**, RM 2,54, gerade, Steckstift 6 mm | **oben** (Körper zeigt zur Analyzer-Platine) | **C50980** (BOOMELE), Extended |

Beides gewöhnliche Massenware. Ausdrücklich **keine Stapelbuchsen**, keine
besonderen Pinlängen — es gibt nichts, was in der Höhe zueinander passen
müsste.

> **Zur Teileauswahl (Stand 30.07.2026):** Die naheliegende Buchsenleiste
> C50982 führt LCSC derzeit als „not available"; deshalb C2977589 mit rund
> 47 000 Stück auf Lager. Beide Positionen sind bei JLCPCB als *Extended*
> geführt (einmalige Einrichtungsgebühr je Teil) und laut Teileseite per
> **Wellenlöten** in Economic *und* Standard PCBA bestückbar.

## Komplettbestückung bei JLCPCB

Möglich — aber es gibt eine Bedingung, die man kennen muss: Die beiden
Leisten sind bedrahtet und sitzen auf **verschiedenen Seiten** der Platine.
Das geht nur mit **Standard PCBA**, das laut Fähigkeitsübersicht „single &
double sided placement (SMT/Thru-hole)" beherrscht; die günstigere
Economic-Variante bestückt nur eine Seite.

Hochladen:

| Schritt | Datei |
| --- | --- |
| Platine | Inhalt von [`fab/gerber/`](fab/gerber/) bzw. das komplette [Fertigungspaket](fab/AskSin-Adapter-J1-fertigung.zip) |
| BOM | [`fab/jlcpcb_bom.csv`](fab/jlcpcb_bom.csv) |
| CPL | [`fab/jlcpcb_cpl.csv`](fab/jlcpcb_cpl.csv) |

Die CPL nennt für J1 ausdrücklich `bottom` und für J2 `top` — beides muss in
der Bestückungsvorschau so ankommen. Weil beide Leisten symmetrische Blöcke
sind, wäre ein Drehfehler um 180° folgenlos; entscheidend ist nur, dass jede
Leiste längs auf ihrer Padreihe liegt und auf der richtigen Seite sitzt.
Pin 1 ist auf beiden Seiten im Bestückungsdruck markiert.

**Die Alternative:** nur die nackte Platine bestellen (ein paar Euro für
fünf Stück) und die zwei Leisten selbst löten. 80 Lötstellen je Platine, aber
ohne Einrichtungsgebühren und ohne Rückfragen zur beidseitigen Bestückung.

## Was der Adapter kostet

- **Bauhöhe:** rund 10 mm zusätzlich im Stapel. Bei der Tray-Höhe im
  19-Zoll-Rahmen berücksichtigen.
- **Versatz:** Die Analyzer-Platine sitzt **2,54 mm weiter hinten** als
  vorgesehen; ihre Bohrungen MH1/MH2 fluchten dann nicht mehr mit den
  Abstandsbolzen des Pi. Im 19-Zoll-Rahmen wird sie ohnehin an der
  Druckhalterung verschraubt; ansonsten helfen Nylon-Distanzstücke.

## Fertigung

2 Lagen, 65 × 14 mm — die einfachste Platine, die ein Hersteller anbietet.
Upload-Paket: [`fab/AskSin-Adapter-J1-fertigung.zip`](fab/AskSin-Adapter-J1-fertigung.zip),
Einzeldateien in [`fab/gerber/`](fab/gerber/), Lagenbild zur Kontrolle in
[`fab/adapter-layout.pdf`](fab/adapter-layout.pdf).

Die Bestückungsseite ist im Druck beschriftet: oben „Analyzer-Platine hier
oben aufstecken", unten „Diese Seite auf den PoE-HAT".

## Prüfung

Erzeugt von [`generate_adapter.py`](generate_adapter.py). Die Netze werden dort
**nach gemessener Pad-Position** vergeben, nicht nach Pad-Nummer — genau die
Verwechslung, an der die Platine v0.0.1 gescheitert ist, kann so nicht mehr
passieren.

Unabhängig davon prüft [`verify_adapter.py`](verify_adapter.py) das fertige
Layout gegen die beiden Gegenstücke und verlangt, dass sich beide Steckbilder
mit **einem einzigen** Versatz decken (jeder abweichende Pin wäre ein falsches
Signal):

```console
$ python3 verify_adapter.py
  A) Unterseite gegen Pi/PoE-HAT: PASST — einheitlicher Versatz +0.00 / +0.00 mm über alle 40 Pins
  B) Oberseite gegen die gefertigte Platine v0.0.1: PASST — einheitlicher Versatz +0.00 / +2.54 mm über alle 40 Pins

Der Adapter passt auf beiden Seiten.
```

Verglichen wird gegen die **offizielle KiCad-Vorlage `RaspberryPi-HAT`** und
gegen den Platinenstand aus dem Git-Tag `hardware-v0.0.1` — also gegen das,
was tatsächlich beim Fertiger lag, nicht gegen den heutigen Entwurf.
DRC: 0 Fehler, 0 Warnungen, 0 unverbundene Elemente.

Vor dem ersten Einschalten trotzdem mit dem Multimeter gegenprüfen (Adapter
gesteckt, Analyzer-Platine gesteckt, Pi **aus**): Durchgang von Pi-Pin 2 (5 V)
zum Eingang von U1 auf der Analyzer-Platine, und **kein** Durchgang zwischen
Pi-Pin 1 (3,3 V) und Masse.

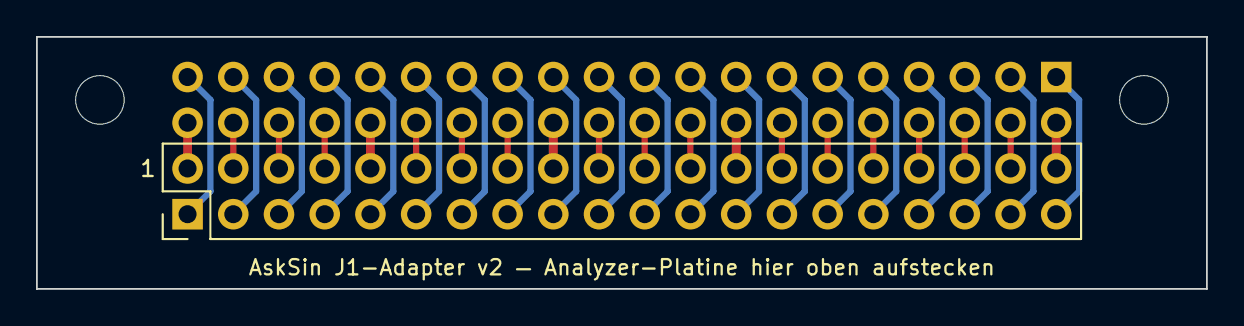
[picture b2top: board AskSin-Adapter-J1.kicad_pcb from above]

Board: 2 copper layers, 65.0 x 14.0 mm, 4 parts (1 on the bottom side), 40 nets.

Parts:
J1: Buchsenleiste 2x20 (unten, zum PoE-HAT); PinSocket_2x20_P2.54mm_Vertical
J2: Stiftleiste 2x20 (oben, zur Platine); PinHeader_2x20_P2.54mm_Vertical
MH1, MH2: MountingHole_2.7mm_M2.5

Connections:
P1: J1.40, J2.2
P2: J1.39, J2.1
P3: J1.38, J2.4
P4: J1.37, J2.3
P5: J1.36, J2.6
P6: J1.35, J2.5
P7: J1.34, J2.8
P8: J1.33, J2.7
P9: J1.32, J2.10
P10: J1.31, J2.9
P11: J1.30, J2.12
P12: J1.29, J2.11
P13: J1.28, J2.14
P14: J1.27, J2.13
P15: J1.26, J2.16
P16: J1.25, J2.15
P17: J1.24, J2.18
P18: J1.23, J2.17
P19: J1.22, J2.20
P20: J1.21, J2.19
P21: J1.20, J2.22
P22: J1.19, J2.21
P23: J1.18, J2.24
P24: J1.17, J2.23
P25: J1.16, J2.26
P26: J1.15, J2.25
P27: J1.14, J2.28
P28: J1.13, J2.27
P29: J1.12, J2.30
P30: J1.11, J2.29
P31: J1.10, J2.32
P32: J1.9, J2.31
P33: J1.8, J2.34
P34: J1.7, J2.33
P35: J1.6, J2.36
P36: J1.5, J2.35
P37: J1.4, J2.38
P38: J1.3, J2.37
P39: J1.2, J2.40
P40: J1.1, J2.39

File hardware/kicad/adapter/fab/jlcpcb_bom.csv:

Comment,Designator,Footprint,JLCPCB Part #
"Buchsenleiste 2x20 RM 2,54 gerade, Hoehe 8,5 mm (ZHOURI 2.54-2*20)",J1,PinSocket_2x20_P2.54mm_Vertical,C2977589
"Stiftleiste 2x20 RM 2,54 gerade, Steckstift 6 mm (BOOMELE 2.54mm 2*20P)",J2,PinHeader_2x20_P2.54mm_Vertical,C50980

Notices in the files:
README.md:
urboot selbst wird **nicht** mitgeliefert: Es steht unter der GPL und gehört
Beschriftung (Name, Version, Datum, Copyright, Lizenz) auf beiden Seiten
Hardware, Doku, Core (dieses Repo) | **CC BY-NC-SA 4.0** | © 2026 S. Sternitzke
Sniffer-Firmware ([eigenes Repo](https://github.com/ssbingo/asksin-sniffer-firmware)) | **CC BY-NC-SA 3.0** | © jp112sdl — abgewandelt, ShareAlike, [Quelle](https://github.com/jp112sdl/AskSinAnalyzer)
Web-UI (`webui/`, eigener Nachbau ohne Fremdcode) | **MIT** | © 2026 S. Sternitzke
AskSinPP (Bibliothek der Firmware) | CC BY-NC-SA 3.0 | pa-pa
